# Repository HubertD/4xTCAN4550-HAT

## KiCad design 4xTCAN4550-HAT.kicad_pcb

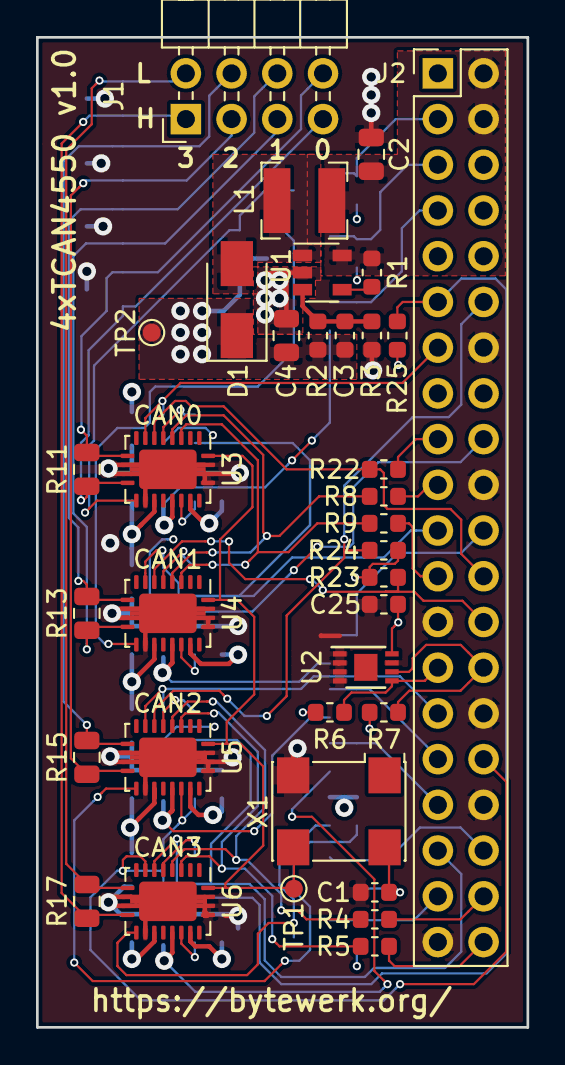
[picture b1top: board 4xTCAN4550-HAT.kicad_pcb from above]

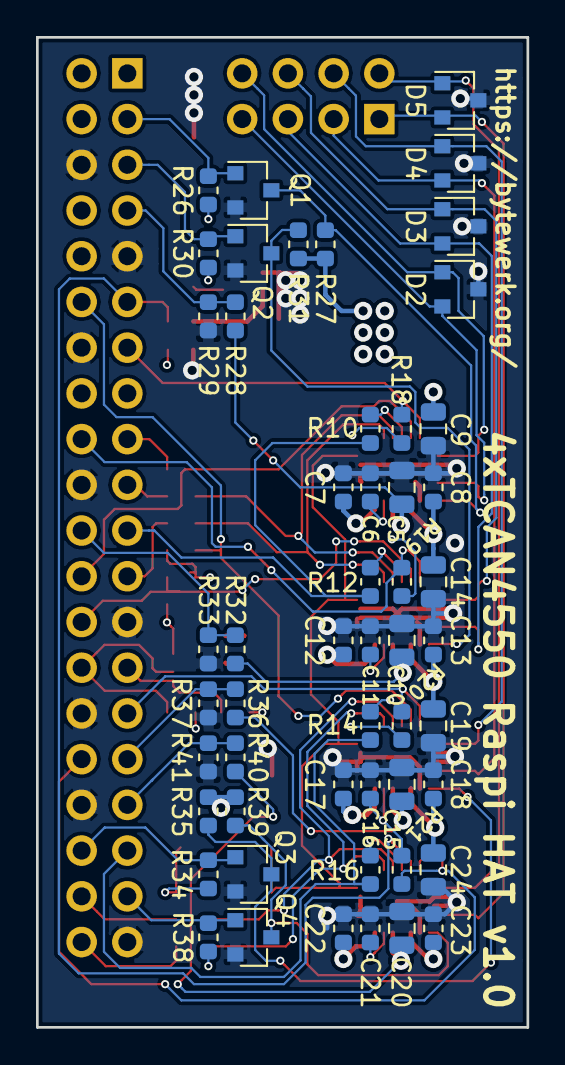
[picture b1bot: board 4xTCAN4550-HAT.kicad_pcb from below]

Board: 4 copper layers, 27.2 x 55.0 mm, 87 parts (52 on the bottom side), 60 nets.

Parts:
C1, C6, C8, C11, C13, C16, C18, C21, C23, C25: 100nF; C_0603_1608Metric
C2, C4, C5, C9, C10, C14, C15, C19, C20, C24: 10uF/10V; C_0805_2012Metric
C3: 470pF; C_0603_1608Metric
C7, C12, C17, C22: 1uF; C_0603_1608Metric
D1: MBRA340; D_SMA
D2, D3, D4, D5: ESDONCAN1; SOT-23
J1: Conn_02x04_Odd_Even; PinHeader_2x04_P2.54mm_Horizontal
J2: Raspberry_Pi_2_3; PinHeader_2x20_P2.54mm_Vertical
L1: SRN4018TA-100M; L_Bourns-SRN4018
Q1, Q2, Q3, Q4: 2N7002; SOT-23
R1: 51K; R_0603_1608Metric
R2: 57K6; R_0603_1608Metric
R3: 13K3; R_0603_1608Metric
R4, R5, R8, R9, R10, R12, R14, R16: 56R; R_0603_1608Metric
R6, R7: 3K9; R_0603_1608Metric
R11, R13, R15, R17: dnp; R_0805_2012Metric
R18, R19, R20, R21, R22, R23, R24, R25, R26, R27, R29, R30, R31, R33, R34, R35, R37, R38, R39, R41: 10K; R_0603_1608Metric
R28, R32, R36, R40: 5K6; R_0603_1608Metric
TP1, TP2: TestPoint; TestPoint_Pad_D1.0mm
U1: LM27313XMF; SOT-23-5
U2: AT24CS64-MAHM; DFN-8-1EP_3x2mm_P0.5mm_EP1.3x1.5mm
U3, U4, U5, U6: TCAN4550; Texas_RGY0020C_EP2.2x3.2mm
X1: ASV-40.000MHz; Oscillator_SMD_Abracon_ASV-4Pin_7.0x5.1mm

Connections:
+3V3: C1.1, C6.1, C11.1, C16.1, C21.1, C25.1, J2.1, J2.17, R6.1, R7.1, R18.1, R19.1, R20.1, R21.1, R22.1, R23.1, R24.1, R25.1, R26.1, R30.1, R34.1, R38.1, U2.8, U3.17, U4.17, U5.17, U6.17, X1.4
+5V: C2.1, J2.2, J2.4, L1.1, R1.1, U1.5
/CAN0/CS: J2.24, R22.2, U3.7
/CAN0/MISO: J2.21, R10.2, R12.2
/CAN0/MOSI: R8.1, U3.5, U4.5
/CAN0/SCK: R9.1, U3.4, U4.4
/CAN0_H: D2.2, J1.7, R11.1, U3.11
/CAN0_L: D2.1, J1.8, R11.2, U3.10
/CAN1/CS: J2.26, R23.2, U4.7
/CAN1_H: D3.2, J1.5, R13.1, U4.11
/CAN1_L: D3.1, J1.6, R13.2, U4.10
/CAN2/CS: J2.12, R24.2, U5.7
/CAN2/MISO: J2.35, R14.2, R16.2
/CAN2/MOSI: R4.2, U5.5, U6.5
/CAN2/SCK: R5.2, U5.4, U6.4
/CAN2_H: D4.2, J1.3, R15.1, U5.11
/CAN2_L: D4.1, J1.4, R15.2, U5.10
/CAN3/CS: J2.11, R25.2, U6.7
/CAN3_H: D5.2, J1.1, R17.1, U6.11
/CAN3_L: D5.1, J1.2, R17.2, U6.10
/CLK_40M: TP1.1, U3.1, U4.1, U5.1, U6.1, X1.3
/Raspi HAT/CAN0_INT: J2.13, R18.2, U3.8
/Raspi HAT/CAN0_IS_AWAKE: J2.7, R28.2, R29.1
/Raspi HAT/CAN0_WAKE: J2.3, Q1.1, R26.2
/Raspi HAT/CAN1_INT: J2.18, R19.2, U4.8
/Raspi HAT/CAN1_IS_AWAKE: J2.22, R32.2, R33.1
/Raspi HAT/CAN1_WAKE: J2.5, Q2.1, R30.2
/Raspi HAT/CAN2_INT: J2.29, R20.2, U5.8
/Raspi HAT/CAN2_IS_AWAKE: J2.31, R36.2, R37.1
/Raspi HAT/CAN2_WAKE: J2.36, Q3.1, R34.2
/Raspi HAT/CAN3_INT: J2.32, R21.2, U6.8
/Raspi HAT/CAN3_IS_AWAKE: J2.33, R40.2, R41.1
/Raspi HAT/CAN3_WAKE: J2.37, Q4.1, R38.2
GND: C1.2, C2.2, C4.2, C5.2, C6.2, C7.2, C8.2, C9.2, C10.2, C11.2, C12.2, C13.2, C14.2, C15.2, C16.2, C17.2, C18.2, C19.2, C20.2, C21.2, C22.2, C23.2, C24.2, C25.2, D2.3, D3.3, D4.3, D5.3, J2.6, J2.9, J2.14, J2.20, J2.25, J2.30, J2.34, J2.39, Q1.2, Q2.2, Q3.2, Q4.2, R3.2, R29.2, R33.2, R37.2, R41.2, U1.2, U2.1, U2.2, U2.3, U2.4, U2.7, U3.13, U3.20, U3.21, U4.13, U4.20, U4.21, U5.13, U5.20, U5.21, U6.13, U6.20, U6.21, X1.2
unnamed: C3.2, R2.2, R3.1, U1.3
unnamed: C5.1, R28.1, U3.16
unnamed: C7.1, U3.18
unnamed: C10.1, R32.1, U4.16
unnamed: C12.1, U4.18
unnamed: C15.1, R36.1, U5.16
unnamed: C17.1, U5.18
unnamed: C20.1, R40.1, U6.16
unnamed: C22.1, U6.18
unnamed: D1.2, L1.2, U1.1
unnamed: J2.19, R8.2
unnamed: J2.23, R9.2
unnamed: J2.27, R6.2, U2.5
unnamed: J2.28, R7.2, U2.6
unnamed: J2.38, R4.1
unnamed: J2.40, R5.1
unnamed: Q1.3, R27.2, U3.12
unnamed: Q2.3, R31.2, U4.12
unnamed: Q3.3, R35.2, U5.12
unnamed: Q4.3, R39.2, U6.12
unnamed: R1.2, U1.4
unnamed: R10.1, U3.6
unnamed: R12.1, U4.6
unnamed: R14.1, U5.6
unnamed: R16.1, U6.6
VCC: C3.1, C4.1, C8.1, C9.1, C13.1, C14.1, C18.1, C19.1, C23.1, C24.1, D1.1, R2.1, R27.1, R31.1, R35.1, R39.1, TP2.1, U3.14, U4.14, U5.14, U6.14

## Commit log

2019-03-01 initial checkin
2019-03-03 add sym-lib-table
2019-03-03 add symbol cache
2019-03-03 fix eeprom
2019-03-04 remove rst, add wake and is_awake
2019-03-07 move wake fet pull-ups from transceivers to raspi-hat schematic page
